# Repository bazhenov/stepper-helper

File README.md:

# Stepper motor tester

Simple stepper motor tester designed around stuff I've had laying around: standart 0.1" perf board, 555 timer, 1117 voltage regulator and some passives.

Oscillator design is 50% duty cycle astable 555 timer.

PCB design has mix of SMD and TH components simply because that is what I have at the moment. It turns out you can mix those types of components quite easily on perfboard :) Ratsnet is showing flywires, tracks are created using solder bridges.

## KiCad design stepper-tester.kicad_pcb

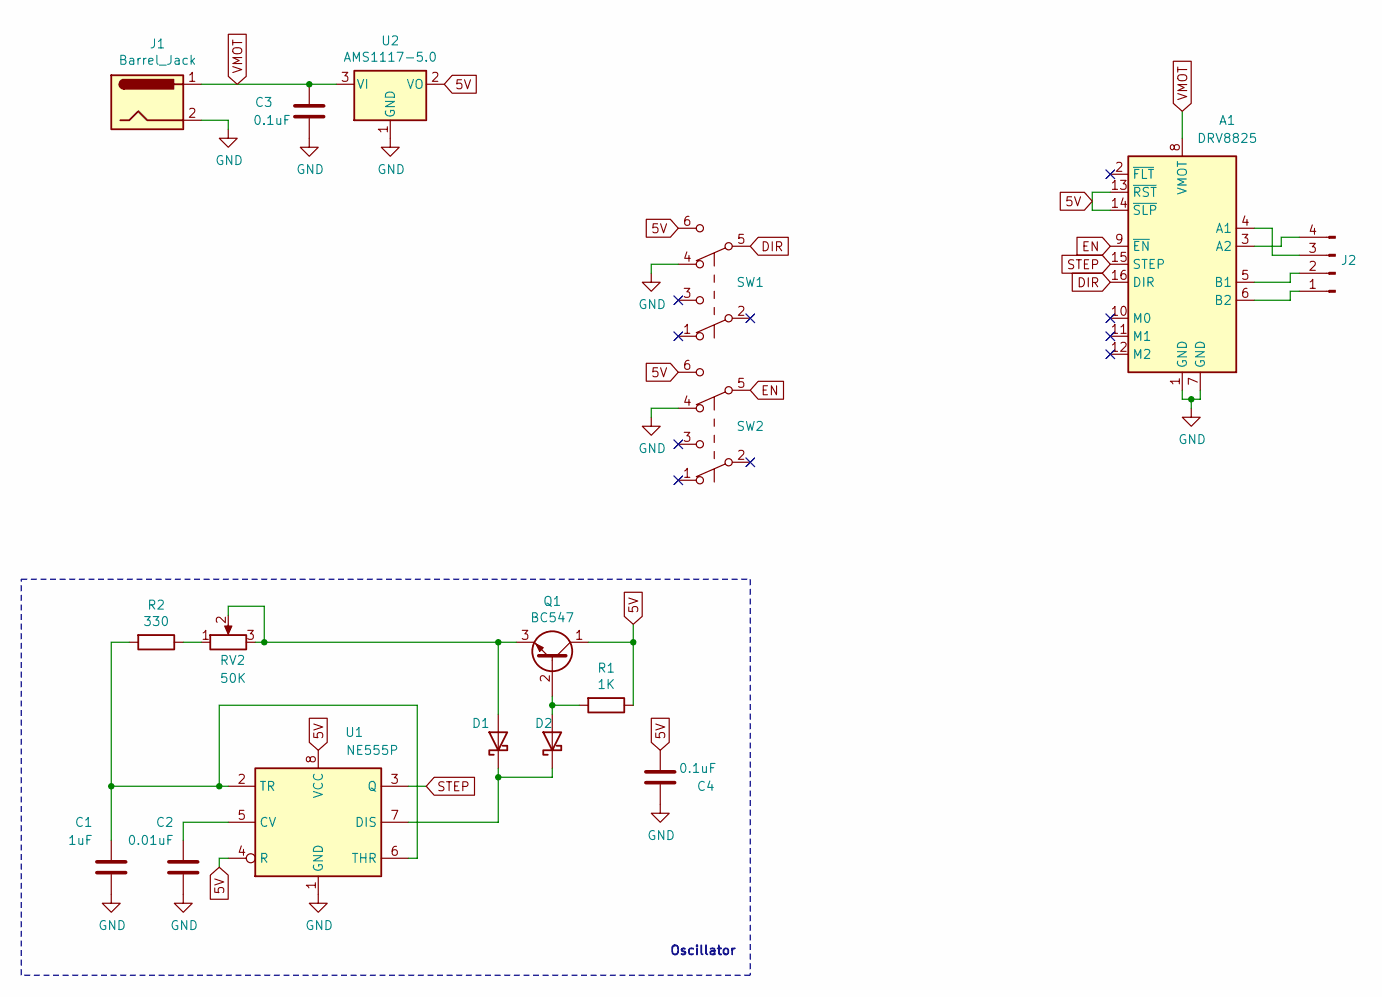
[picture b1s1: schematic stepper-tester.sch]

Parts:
A1: DRV8825; Pololu_Breakout-16_15.2x20.3mm
C1: 1uF; C_Disc_D4.3mm_W1.9mm_P5.00mm
C2: 0.01uF; C_Disc_D4.3mm_W1.9mm_P5.00mm
C3, C4: 0.1uF; C_0805_2012Metric_Pad1.18x1.45mm_HandSolder
D1, D2: 1N5817; D_DO-41_SOD81_P10.16mm_Horizontal
J1: Barrel_Jack; TerminalBlock_bornier-2_P5.08mm
J2: Conn_01x04_Male; PinSocket_1x04_P2.54mm_Vertical
Q1: BC547; TO-92L_Inline_Wide
R1: 1K; R_Axial_DIN0207_L6.3mm_D2.5mm_P2.54mm_Vertical
R2: 330; R_Axial_DIN0204_L3.6mm_D1.6mm_P7.62mm_Horizontal
RV2: 50K; PinHeader_1x03_P2.54mm_Vertical
SW1, SW2: SW_Push_DPDT; SW_NKK_GW12LJP
U1: NE555P; SO-8_5.3x6.2mm_P1.27mm
U2: AMS1117-5.0; SOT-223-3_TabPin2

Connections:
5V: A1.13 (~RST), A1.14 (~SLP), C4.1, Q1.1 (C), R1.1, SW1.6 (C), SW2.6 (C), U1.4 (R), U1.8 (VCC), U2.2 (VO)
DIR: A1.16 (DIR), SW1.5 (B)
EN: A1.9 (~EN), SW2.5 (B)
GND: A1.1 (GND), A1.7 (GND), C1.1, C2.1, C3.1, C4.2, J1.2, SW1.4 (A), SW2.4 (A), U1.1 (GND), U2.1 (GND)
unnamed: A1.3 (A2), J2.4
unnamed: A1.4 (A1), J2.3
unnamed: A1.5 (B1), J2.2
unnamed: A1.6 (B2), J2.1
unnamed: C1.2, R2.2, U1.2 (TR), U1.6 (THR)
unnamed: C2.2, U1.5 (CV)
unnamed: D1.1 (K), D2.1 (K), U1.7 (DIS)
unnamed: D1.2 (A), Q1.3 (E), RV2.2, RV2.3
unnamed: D2.2 (A), Q1.2 (B), R1.2
unnamed: R2.1, RV2.1
STEP: A1.15 (STEP), U1.3 (Q)
VMOT: A1.8 (VMOT), C3.2, J1.1, U2.3 (VI)

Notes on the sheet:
Oscillator

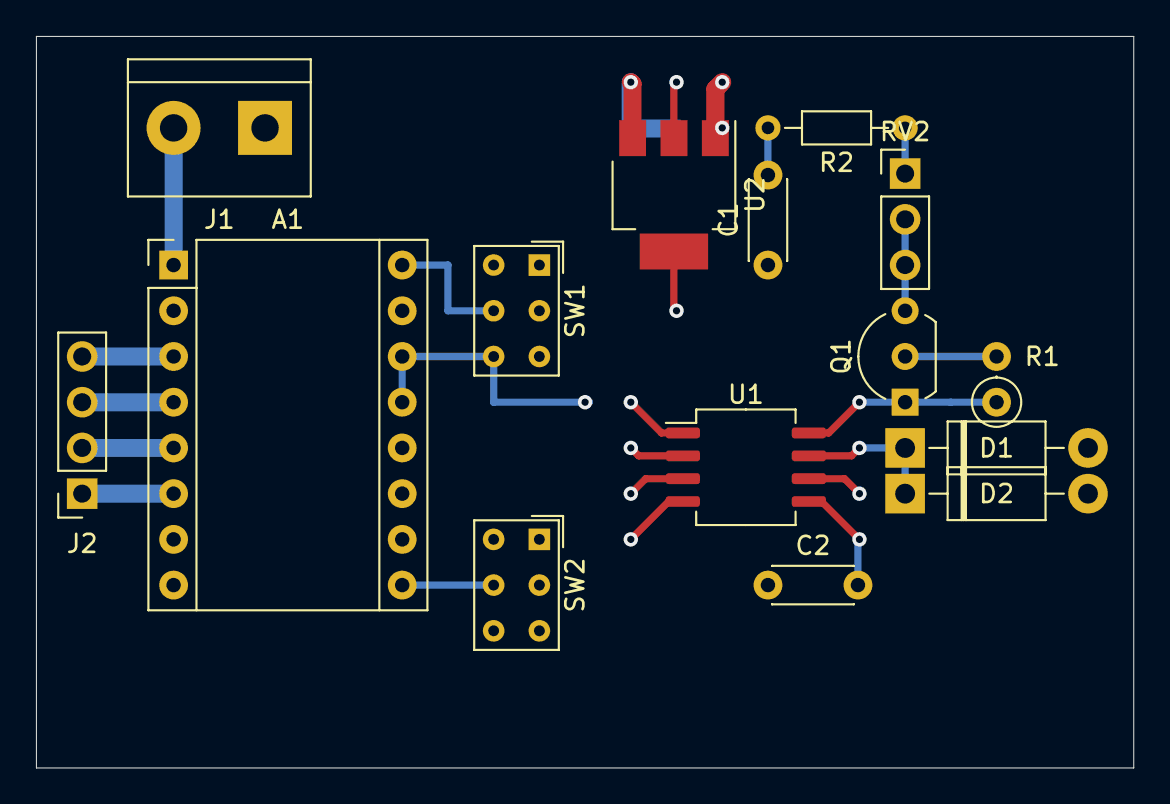
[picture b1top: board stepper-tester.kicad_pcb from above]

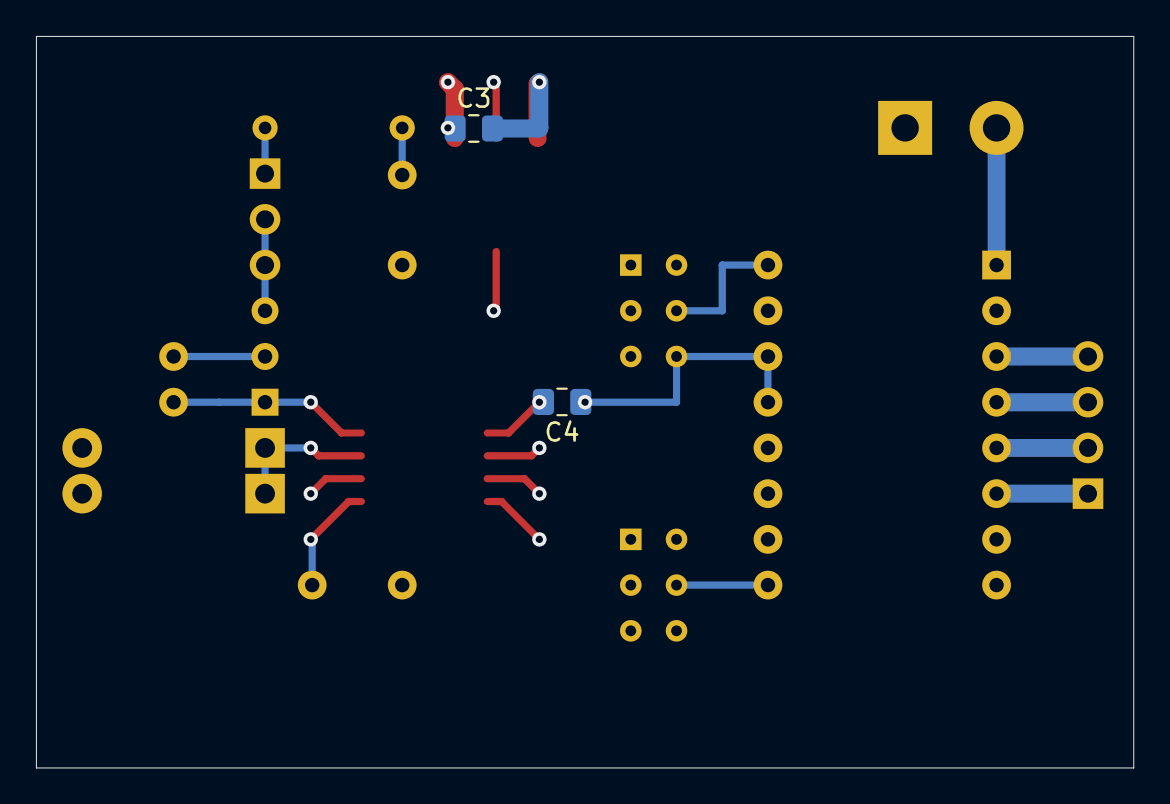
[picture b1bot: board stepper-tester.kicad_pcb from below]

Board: 2 copper layers, 61.0 x 40.6 mm, 17 parts (2 on the bottom side), 16 nets.

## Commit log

2020-07-29 Kicad update
2020-07-30 Update schematics
2020-08-01 NE555 schematic verified
2020-08-02 All footprints associated
2020-08-04 PCB cleanup
2020-08-09 new layout
2020-10-06 50% duty cycle 555 schematics
2020-10-07 PCB WIP
2020-11-21 Add readme
